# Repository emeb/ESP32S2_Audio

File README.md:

# ESP32S2_Audio
A Eurorack module demonstrating the use of the ESP32S2 as an audio effects processor

## Abstract
Blah Blah Blah 2020 Microcontroller shortage. See my RP2040_Audio project
if you really want to read all my whinging about this topic:

https://github.com/emeb/RP2040_Audio

So yeah - I've been using STM32 for so long that I was ignoring all this other
stuff that was coming out, including these nifty IoT SoCs (more TLAS pls!) that
so many folks have been using for the lst few years. Espressif has quite a
family of them with a wide variety of capabilities. The ESP32-S2FN4R2 is
especially interesting because it's got 4MB flash and 2MB PSRAM included in
the package and the price is only a few cents more than the raw part. So I
grabbed some devboards, did proof-of-concept on a breadboard and started a
new hardware design. This one is remarkably similar to the RP2040 project
mentioned above - basically I lifted the entire circuit, layout and all and
then proceeded to jack it up on the grease rack and swap the engine out. Here's
the result.

This project is a feasibility study of using the ESP32S2 MCU as an audio effects
processor, with particular emphasis on performance with challenging DSP.

## Hardware
The complete design consists of two PCBs:
* The system PCB - a single board containg all electrical components. Find it
in the Hardware directory.
* The Front Panel - a PCB-based front panel that conforms to the Eurorack
physical mounting standard. Found in the Hardware/esp32s2_panel directory.

The system PCB has the following features:
* Standard Eurorack 16-pin shrouded power connector
* Two +/-5V CV inputs and associated analog signal conditioning 
* Two +/-7V Audio inputs and associated analog signal conditioning 
* Two +/-7V Audio outputs and associated analog drivers
* WM8731 stereo audio codec
* ESP32S2 with 4MB SPI flash, 2MB PSRAM, USB, JTAG and serial interfaces for
development. The RF antenna connection is also available for playing with WiFi
if I ever get around to it.
* 160 x 80 IPS LCD
* UI button

## Firmware
A demonstration firmware is included that exercises all of the capabilities of
the system, including the LCD, UI button, CV inputs and stereo audio I/O. It is
a basic multi-effects unit that supports a complement of audio DSP algorithms
that are easily extended by adding standardized modules to a data structure.
As provided here just three algorithms are available:
* Simple pass-thru with no processing
* Simple gain control
* Basic "clean delay" with crossfaded deglitching during delay changes.

Other algorithms have been tested including phasers, flangers, frequency shifters,
resampling delays and reverbs, but these are not publicly released at this time.

## Findings
The ESP32S2 is not bad for doing audio, but I found it necessary to do a bit of
hacking on their I2S driver - as delivered in their ESP-IDF V5.0 which I used
here the driver makes some limiting assumptions about how you want to do audio:
Namely that you'll be streaming large buffers to/from some external device like
the WiFi interface or storage. That's *NOT* how I do audio - I want small
buffers streaming in realtime with lots of DSP involved. Consequently, I coded
up a "low-latency" driver that works more the way I want and that's included
here.

The ESP32 ADCs are also noisy and a bit weird to use, so my ADC driver has a
rather kludgy approach to collecting data and applies heavy filtering to clean
things up. The lack of hardware floating point was a bit of a stumbling block
and I spent some time converting a few of my algorithms to work with fixed
point. A few others were fine using floating point in software so those were
left alone. The reasonably large PSRAM works well for smaller-sized buffers
in audio delays and found a lot of use in delays.

I found many other aspects of their system quite pleasant to use - the IDF has
a lot of well thought-out services, and the build process is easy to work with.

TL;DR - ESP32S2 can work well for audio effects. Give it a try!

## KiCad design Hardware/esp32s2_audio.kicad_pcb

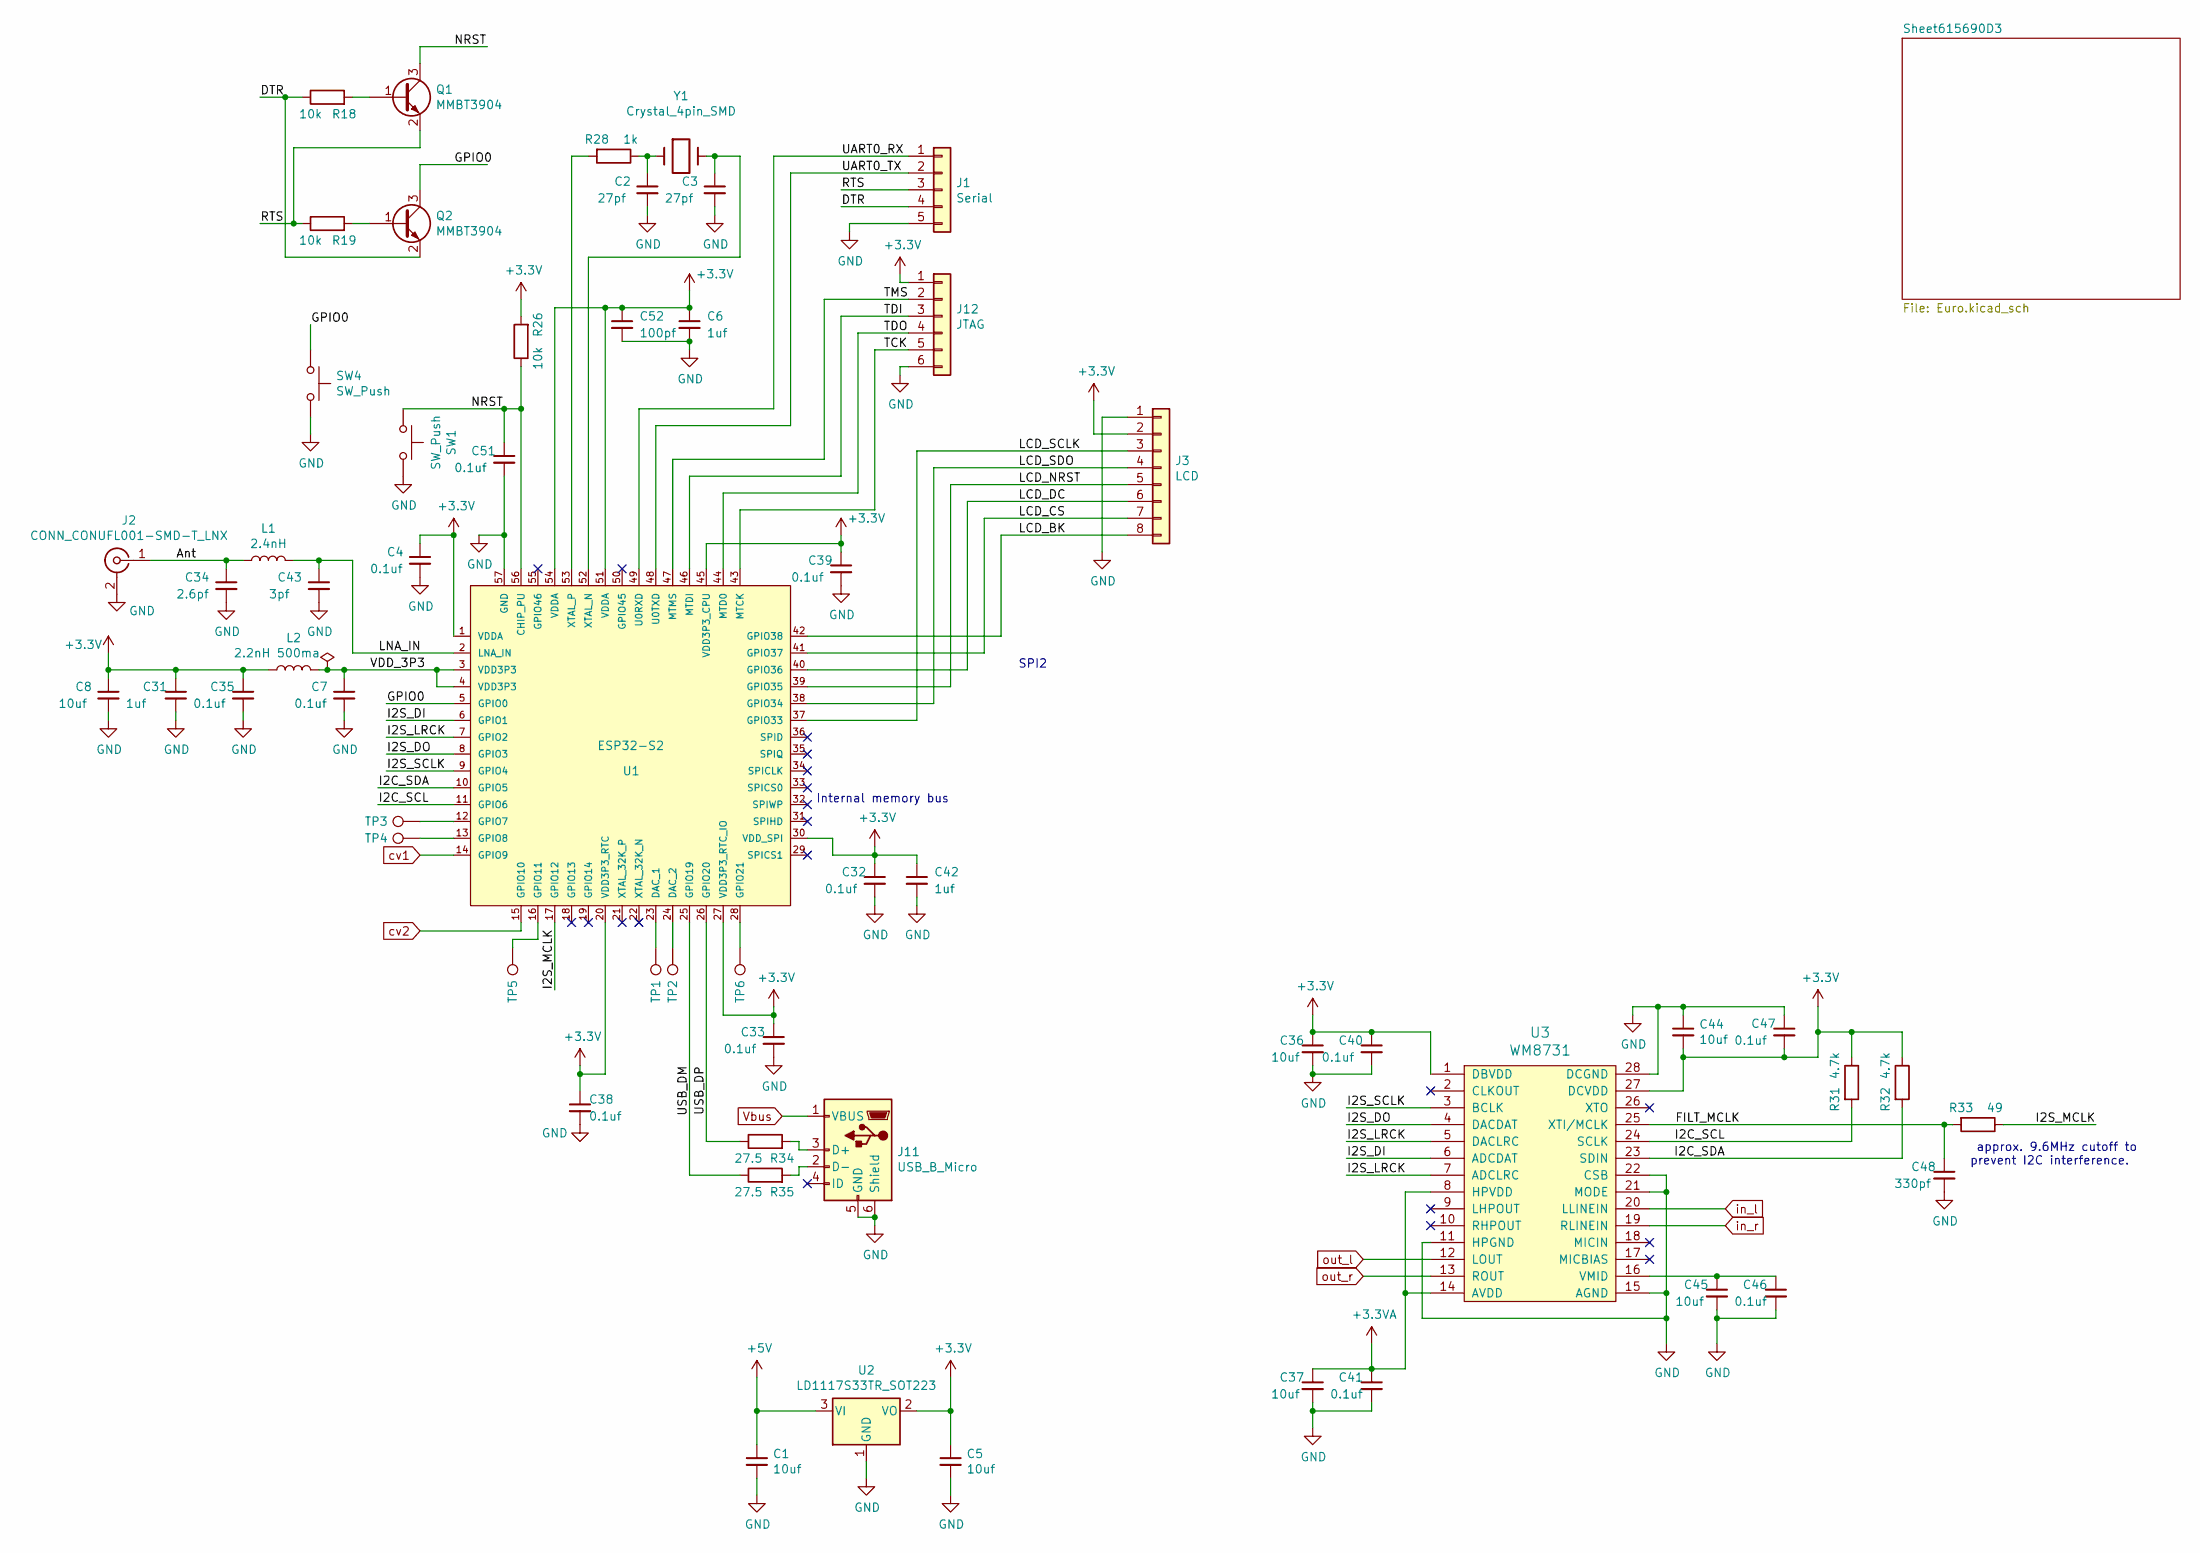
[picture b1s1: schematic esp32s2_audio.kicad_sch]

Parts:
C1, C5, C8, C36, C37, C44, C45: 10uf; C_0805
C2, C3: 27pf; C_0603
C4, C7, C32, C33, C35, C38, C39, C40, C41, C46, C47, C51: 0.1uf; C_0603
C6, C31, C42: 1uf; C_0603
C34: 2.6pf; C_0603
C43: 3pf; C_0603
C48: 330pf; C_0603
C52: 100pf; C_0603
J1: Serial; Pin_Header_Straight_1x05_Pitch2.54mm
J2: CONN_CONUFL001-SMD-T_LNX; CONUFL001-SMD-T
J3: LCD; LCD_80x160_0.96
J11: USB_B_Micro; USB_Micro-B_10103594-0001LF_actual_outline
J12: JTAG; Pin_Header_Straight_1x06_Pitch2.54mm
L1: 2.4nH; C_0603_1608Metric
L2: 2.2nH 500ma; C_0603_1608Metric
Q1, Q2: MMBT3904; SOT-23
R18, R19, R26: 10k; R_0603
R28: 1k; R_0603
R31, R32: 4.7k; R_0603
R33: 49; R_0603
R34, R35: 27.5; R_0603
SW1: SW_Push; SW_SPST_KMR2
SW4: SW_Push; SW_PUSH_6mm_Center
TP1, TP2, TP3, TP4, TP5, TP6: TestPoint; Measurement_Point_Round-SMD-Pad_Small
U1: ESP32-S2; Espressif_Systems-ESP32-S2-IPC_A; mouser part number 356-ESP32-S2; digikey description RX TXRX MOD WIFI SURFACE MOUNT
U2: LD1117S33TR_SOT223; SOT-223-3_TabPin2
U3: WM8731; SSOP-28_5.3x10.2mm_Pitch0.65mm
Y1: Crystal_4pin_SMD; Crystal_SMD_3225-4pin_3.2x2.5mm

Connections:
+3.3VA: C37.1, C41.1, U3.8 (HPVDD), U3.14 (AVDD); also elsewhere on the board
+3V3: C4.1, C5.1, C6.1, C8.1, C31.1, C32.1, C33.1, C35.1, C36.1, C38.1, C39.1, C40.1, C42.1, C44.2, C47.2, C52.1, J3.2, J12.1, L2.1, R26.2, R31.1, R32.1, U1.1 (VDDA), U1.20 (VDD3P3_RTC), U1.27 (VDD3P3_RTC_IO), U1.30 (VDD_SPI), U1.45 (VDD3P3_CPU), U1.51 (VDDA), U1.54 (VDDA), U2.2 (VO), U3.1 (DBVDD), U3.27 (DCVDD)
+5V: C1.1, U2.3 (VI); also elsewhere on the board
/Ant: C34.1, J2.1 (SIG), L1.1
/DTR: J1.4, Q2.2 (E), R18.1
/FILT_MCLK: C48.1, R33.2, U3.25 (XTI/MCLK)
/GPIO0: Q2.3 (C), SW4.1, U1.5 (GPIO0)
/I2C_SCL: R31.2, U1.11 (GPIO6), U3.24 (SCLK)
/I2C_SDA: R32.2, U1.10 (GPIO5), U3.23 (SDIN)
/I2S_DI: U1.6 (GPIO1), U3.6 (ADCDAT)
/I2S_DO: U1.8 (GPIO3), U3.4 (DACDAT)
/I2S_LRCK: U1.7 (GPIO2), U3.5 (DACLRC), U3.7 (ADCLRC)
/I2S_MCLK: R33.1, U1.17 (GPIO12)
/I2S_SCLK: U1.9 (GPIO4), U3.3 (BCLK)
/LCD_BK: J3.8, U1.42 (GPIO38)
/LCD_CS: J3.7, U1.41 (GPIO37)
/LCD_DC: J3.6, U1.40 (GPIO36)
/LCD_NRST: J3.5, U1.39 (GPIO35)
/LCD_SCLK: J3.3, U1.37 (GPIO33)
/LCD_SDO: J3.4, U1.38 (GPIO34)
/LNA_IN: C43.1, L1.2, U1.2 (LNA_IN)
/NRST: C51.1, Q1.3 (C), R26.1, SW1.1, U1.56 (CHIP_PU)
/RTS: J1.3, Q1.2 (E), R19.1
/TCK: J12.5, U1.43 (MTCK)
/TDI: J12.3, U1.46 (MTDI)
/TDO: J12.4, U1.44 (MTD0)
/TMS: J12.2, U1.47 (MTMS)
/UART0_RX: J1.1, U1.49 (U0RXD)
/UART0_TX: J1.2, U1.48 (U0TXD)
/USB_DM: R35.1, U1.25 (GPIO19)
/USB_DP: R34.1, U1.26 (GPIO20)
/VDD_3P3: C7.1, L2.2, U1.3 (VDD3P3), U1.4 (VDD3P3)
GND: C1.2, C2.2, C3.2, C4.2, C5.2, C6.2, C7.2, C8.2, C31.2, C32.2, C33.2, C34.2, C35.2, C36.2, C37.2, C38.2, C39.2, C40.2, C41.2, C42.2, C43.2, C44.1, C45.2, C46.2, C47.1, C48.2, C51.2, C52.2, J1.5, J2.2 (GND), J3.1, J11.5 (GND), J11.6 (Shield), J12.6, SW1.2, SW4.2, U1.57 (GND), U2.1 (GND), U3.11 (HPGND), U3.15 (AGND), U3.21 (MODE), U3.22 (CSB), U3.28 (DCGND); also elsewhere on the board
unnamed: C2.1, R28.1, Y1.1
unnamed: C3.1, U1.52 (XTAL_N), Y1.3
unnamed: C45.1, C46.1, U3.16 (VMID)
unnamed: J11.2 (D-), R35.2
unnamed: J11.3 (D+), R34.2
unnamed: Q1.1 (B), R18.2
unnamed: Q2.1 (B), R19.2
unnamed: R28.2, U1.53 (XTAL_P)
unnamed: TP1.1, U1.23 (DAC_1)
unnamed: TP2.1, U1.24 (DAC_2)
unnamed: TP3.1, U1.12 (GPIO7)
unnamed: TP4.1, U1.13 (GPIO8)
unnamed: TP5.1, U1.16 (GPIO11)
unnamed: TP6.1, U1.28 (GPIO21)
Vbus: J11.1 (VBUS); also elsewhere on the board
cv1: U1.14 (GPIO9); also elsewhere on the board
cv2: U1.15 (GPIO10); also elsewhere on the board
in_l: U3.20 (LLINEIN); also elsewhere on the board
in_r: U3.19 (RLINEIN); also elsewhere on the board
out_l: U3.12 (LOUT); also elsewhere on the board
out_r: U3.13 (ROUT); also elsewhere on the board

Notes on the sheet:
SPI2
Internal memory bus
approx. 9.6MHz cutoff to prevent I2C interference.

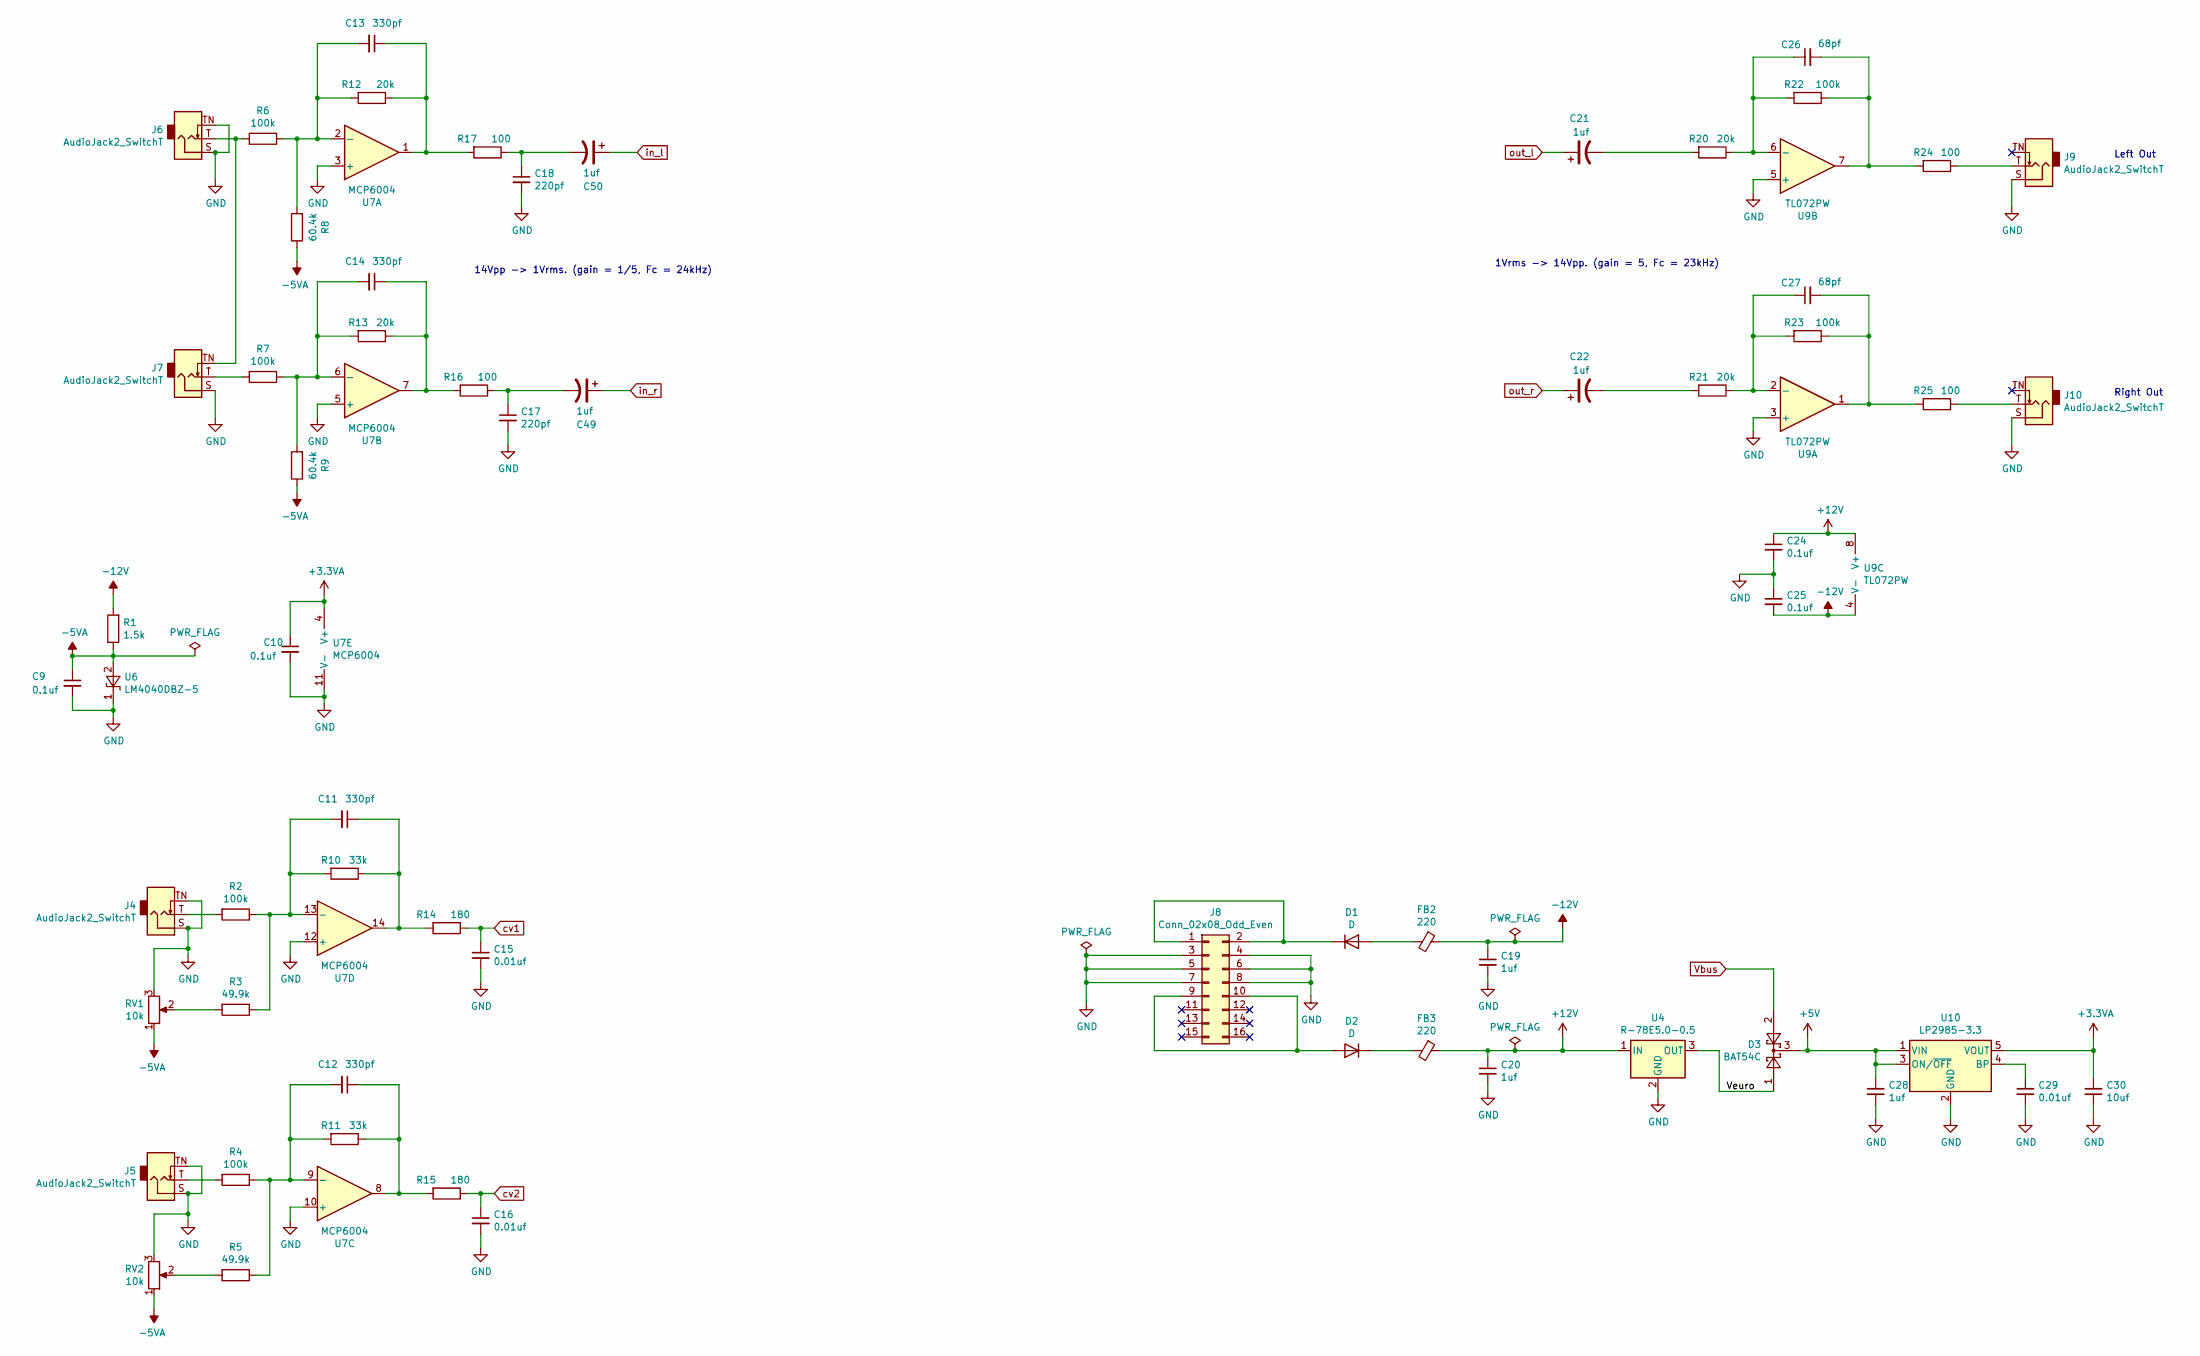
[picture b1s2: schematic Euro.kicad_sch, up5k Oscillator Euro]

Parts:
C9, C10, C24, C25: 0.1uf; C_0603
C11, C12, C13, C14: 330pf; C_0603
C15, C16, C29: 0.01uf; C_0603
C17, C18: 220pf; C_0603
C19, C20, C28: 1uf; C_0603
C21, C22, C49, C50: 1uf; CP_Elec_4x5.3
C26, C27: 68pf; C_0603
C30: 10uf; C_0805
D1, D2: D; D_SMA
D3: BAT54C; SOT-23
FB2, FB3: 220; R_0805
J4, J5, J6, J7, J9, J10: AudioJack2_SwitchT; Jack_3.5mm_QingPu_WQP-PJ398SM_Vertical_CircularHoles
J8: Conn_02x08_Odd_Even; 5103308-3
R1: 1.5k; R_0603
R2, R4, R6, R7, R22, R23: 100k; R_0603
R3, R5: 49.9k; R_0603
R8, R9: 60.4k; R_0603
R10, R11: 33k; R_0603
R12, R13, R20, R21: 20k; R_0603
R14, R15: 180; R_0603
R16, R17, R24, R25: 100; R_0603
RV1, RV2: 10k; Potentiometer_TT_P0915N
U4: R-78E5.0-0.5; Converter_DCDC_RECOM_R-78E-0.5_THT
U6: LM4040DBZ-5; SOT-23
U7: MCP6004; TSSOP-14_4.4x5mm_Pitch0.65mm
U9: TL072PW; TSSOP-8_4.4x3mm_Pitch0.65mm
U10: LP2985-3.3; SOT-23-5

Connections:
+3.3VA: C10.1, C30.1, U7.4 (V+), U10.5 (VOUT); also elsewhere on the board
+5V: C28.1, D3.3, U10.1 (VIN), U10.3 (ON/~OFF); also elsewhere on the board
+12V: C20.1, C24.1, FB3.1, U4.1 (IN), U9.8 (V+)
-5VA: C9.1, R1.1, R8.1, R9.1, RV1.1, RV2.1, U6.2 (A)
-12V: C19.1, C25.2, FB2.1, R1.2, U9.4 (V-)
/Sheet615690D3/Veuro: D3.1, U4.3 (OUT)
GND: C9.2, C10.2, C15.2, C16.2, C17.2, C18.2, C19.2, C20.2, C24.2, C25.1, C28.2, C29.2, C30.2, J4.S, J4.TN, J5.S, J5.TN, J6.S, J6.TN, J7.S, J8.3, J8.4, J8.5, J8.6, J8.7, J8.8, J9.S, J10.S, RV1.3, RV2.3, U4.2 (GND), U6.1 (K), U7.3 (+), U7.5 (+), U7.10 (+), U7.11 (V-), U7.12 (+), U9.3 (+), U9.5 (+), U10.2 (GND); also elsewhere on the board
unnamed: C11.1, R10.1, R14.2, U7.14
unnamed: C11.2, R2.1, R3.1, R10.2, U7.13 (-)
unnamed: C12.1, R11.1, R15.2, U7.8
unnamed: C12.2, R4.1, R5.1, R11.2, U7.9 (-)
unnamed: C13.1, R12.1, R17.2, U7.1
unnamed: C13.2, R6.1, R8.2, R12.2, U7.2 (-)
unnamed: C14.1, R13.1, R16.2, U7.7
unnamed: C14.2, R7.1, R9.2, R13.2, U7.6 (-)
unnamed: C17.1, C49.2, R16.1
unnamed: C18.1, C50.2, R17.1
unnamed: C21.2, R20.2
unnamed: C22.2, R21.2
unnamed: C26.1, R20.1, R22.2, U9.6 (-)
unnamed: C26.2, R22.1, R24.2, U9.7
unnamed: C27.1, R21.1, R23.2, U9.2 (-)
unnamed: C27.2, R23.1, R25.2, U9.1
unnamed: C29.1, U10.4 (BP)
unnamed: D1.1 (K), J8.1, J8.2
unnamed: D1.2 (A), FB2.2
unnamed: D2.1 (K), FB3.2
unnamed: D2.2 (A), J8.9, J8.10
unnamed: J4.T, R2.2
unnamed: J5.T, R4.2
unnamed: J6.T, J7.TN, R6.2
unnamed: J7.T, R7.2
unnamed: J9.T, R24.1
unnamed: J10.T, R25.1
unnamed: R3.2, RV1.2
unnamed: R5.2, RV2.2
Vbus: D3.2; also elsewhere on the board
cv1: C15.1, R14.1; also elsewhere on the board
cv2: C16.1, R15.1; also elsewhere on the board
in_l: C50.1; also elsewhere on the board
in_r: C49.1; also elsewhere on the board
out_l: C21.1; also elsewhere on the board
out_r: C22.1; also elsewhere on the board

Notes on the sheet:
14Vpp -> 1Vrms. (gain = 1/5, Fc = 24kHz)
Left Out
1Vrms -> 14Vpp. (gain = 5, Fc = 23kHz)
Right Out

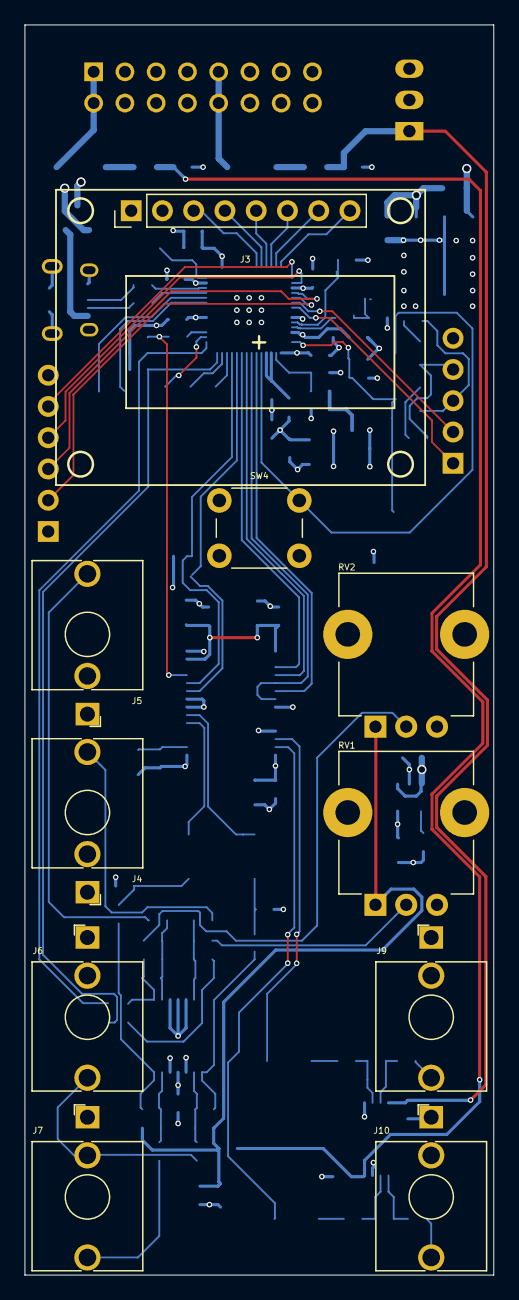
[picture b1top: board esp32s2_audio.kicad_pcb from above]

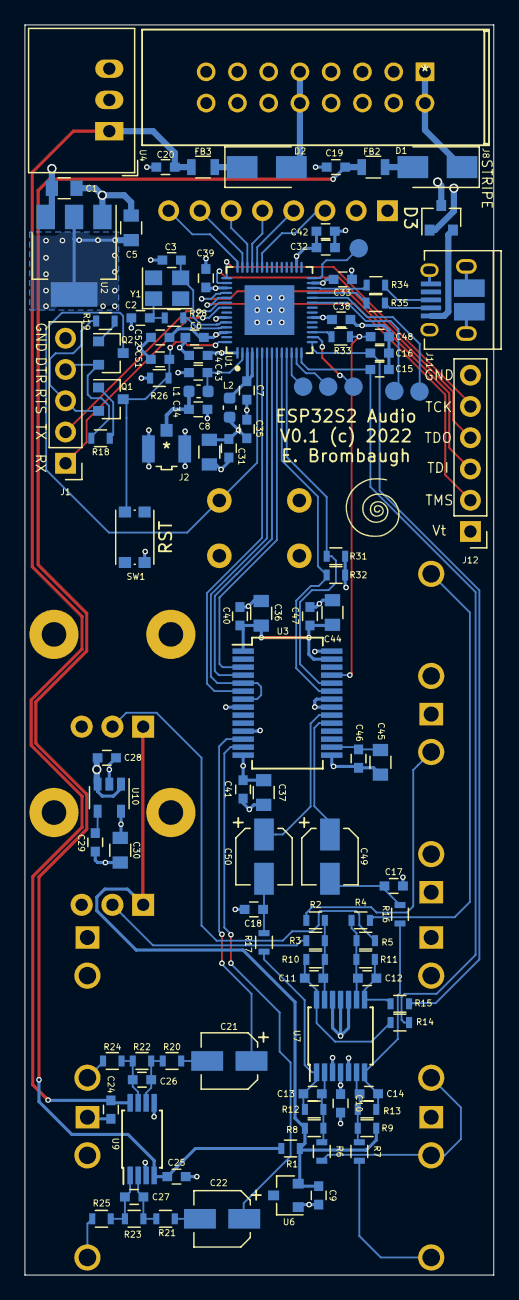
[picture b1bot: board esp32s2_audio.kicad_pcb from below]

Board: 4 copper layers, 38.1 x 101.6 mm, 124 parts (114 on the bottom side), 87 nets.

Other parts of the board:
Ref**: Val**; avatar_small

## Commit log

2022-04-11 Initial commit of ESP32S2_Audio stuff

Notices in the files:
Hardware/esp32s2_audio.kicad_pcb:
V0.1 (c) 2022
parts and their libraries:
Copyright 2016 Accelerated Designs. All rights reserved.
Copyright 2021 Accelerated Designs. All rights reserved.
